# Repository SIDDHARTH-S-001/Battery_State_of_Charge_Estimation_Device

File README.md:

# Battery_State_of_Charge_Estimation_Device

<h3>Introduction</h3>
<br>This is a deep learning approach to estimate State-of-Charge of 18650 Li-Ion batteries in real-time with high accuracy.</br>

<br>The dataset, used can be found here, [Dataset](https://data.mendeley.com/datasets/cp3473x7xv/1).
<br>Clone this repo into your working directory and execute the **training_code.m** file to train an artifical neural network.
<br>You can change the network hyper-parameters to improve training results.
<br>Once the training is complete, you can export the model into various formats as per your use case through builtin matlab commands. In this case, it has been exported as a Tensorflow model and later converted to TFLite format to be deployed on Hardware.
<br>Matlab Code files have been written in Matlab 2020b and all python files have been verified to work in Python 3.9

<br>The Schematic and board files for the PCB HAT designed for Raspberry Pi can be found in the [PCB](https://github.com/SIDDHARTH-S-001/Battery_State_of_Charge_Estimation_Device/tree/main/PCB) folder. These were designed in [Eagle](https://www.autodesk.com/products/eagle/overview?term=1-YEAR&tab=subscription) 9.6.2

<h3>Components</h3>
<br>1) Raspberry Pi 4</br>
<br>2) 3Ah 18650 Li-Ion cell</br>
<br>3) 0-25V Generic Voltage sensor</br>
<br>4) 0-30A ACS712 Current Sensor</br>
<br>5) DHT11 Temperature Humidity Sensor</br>
<br>6) ADS1115 / MCP3208 (ADC)</br>

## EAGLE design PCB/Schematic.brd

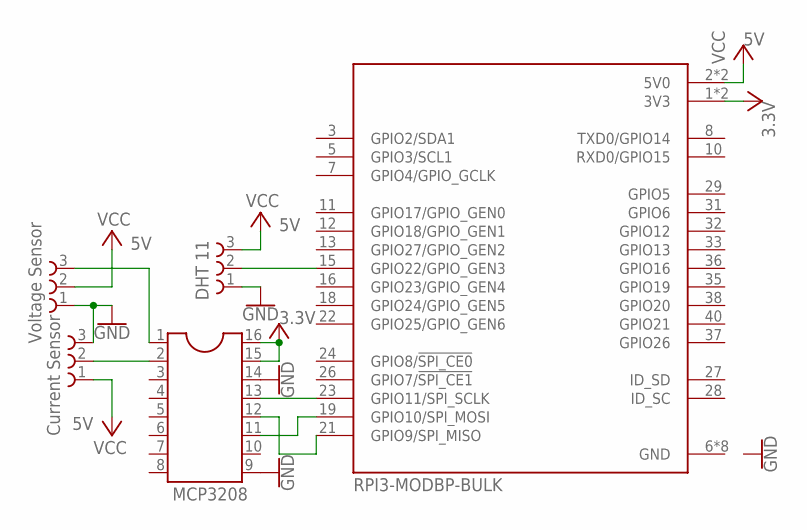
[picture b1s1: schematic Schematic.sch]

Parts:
IC1: MCP3208; SOCKET-16
J1: Current Sensor; 61300311821
J2: Voltage Sensor; 61300311821
J3: DHT 11; 61300311821
U1: RPI3-MODBP-BULK; MODULE_RPI3-MODBP-BULK

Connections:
GND: IC1.9, IC1.14, J1.3, J2.1, J3.1, U1.6 (GND), U1.9 (GND), U1.14 (GND), U1.20 (GND), U1.25 (GND), U1.30 (GND), U1.34 (GND), U1.39 (GND)
unnamed: IC1.13, U1.23 (GPIO11/SPI_SCLK)
unnamed: IC1.11, U1.19 (GPIO10/SPI_MOSI)
unnamed: IC1.12, U1.21 (GPIO9/SPI_MISO)
unnamed: IC1.1, J2.3
unnamed: IC1.2, J1.2
unnamed: J3.2, U1.15 (GPIO22/GPIO_GEN3)
VCC: IC1.15, IC1.16, J1.1, J2.2, J3.3, U1.1 (3V3), U1.2 (5V0), U1.4 (5V0), U1.17 (3V3)

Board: 2 copper layers, 5 parts (0 on the bottom side), 8 nets, no tracks yet.

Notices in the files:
parts and their libraries:
SparkFun-PowerSymbols: Licensing: Creative Commons ShareAlike 4.0 International - https://creativecommons.org/licenses/by-sa/4.0
